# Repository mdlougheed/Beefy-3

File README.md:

# Meaty-3+
Meaty-3+ is a micro USB connected Basic Breakout for the FTDI FT231XS USB to serial IC. It's a "springboard" from the Sparkfun "Beefy-3" USB-Serial board with some additional capabilities.

Version 3 includes an improved micro-USB plug and updated documents.

Boards are available from OSH Park:<a href="https://oshpark.com/shared_projects/OyBMIKnf"></img></a>

The Meaty-3+ brings more power output, using a Torex Semiconductor 1 Amp XC6220B331MR-G linear 3.3V regulator. That's a whopping 66% power output increase (up to your USB power supply current limit - of course)! It also features on-board selectable CTS input or RTS output using a solder jumper.

This board will auto-reset any Arduino board that has the (DTR) reset pin brought out to a 6-pin connector (Arduino, Lilypad, etc) - AND can be configured for auto-resetting boards that use the RTS signal, as well as auto-reset/auto-program ESP-8266 & EPS-32 based boards that use the NodeMCU style DTR/RTS transistor crossover reset circuit (NodeMCU, ESP8266, ESP-01, Huzzah). In other words, you have flexibility!

This pluggable serial adapter, simplifies your application board when the power and cost expense of USB serial connectivity isn't always needed.

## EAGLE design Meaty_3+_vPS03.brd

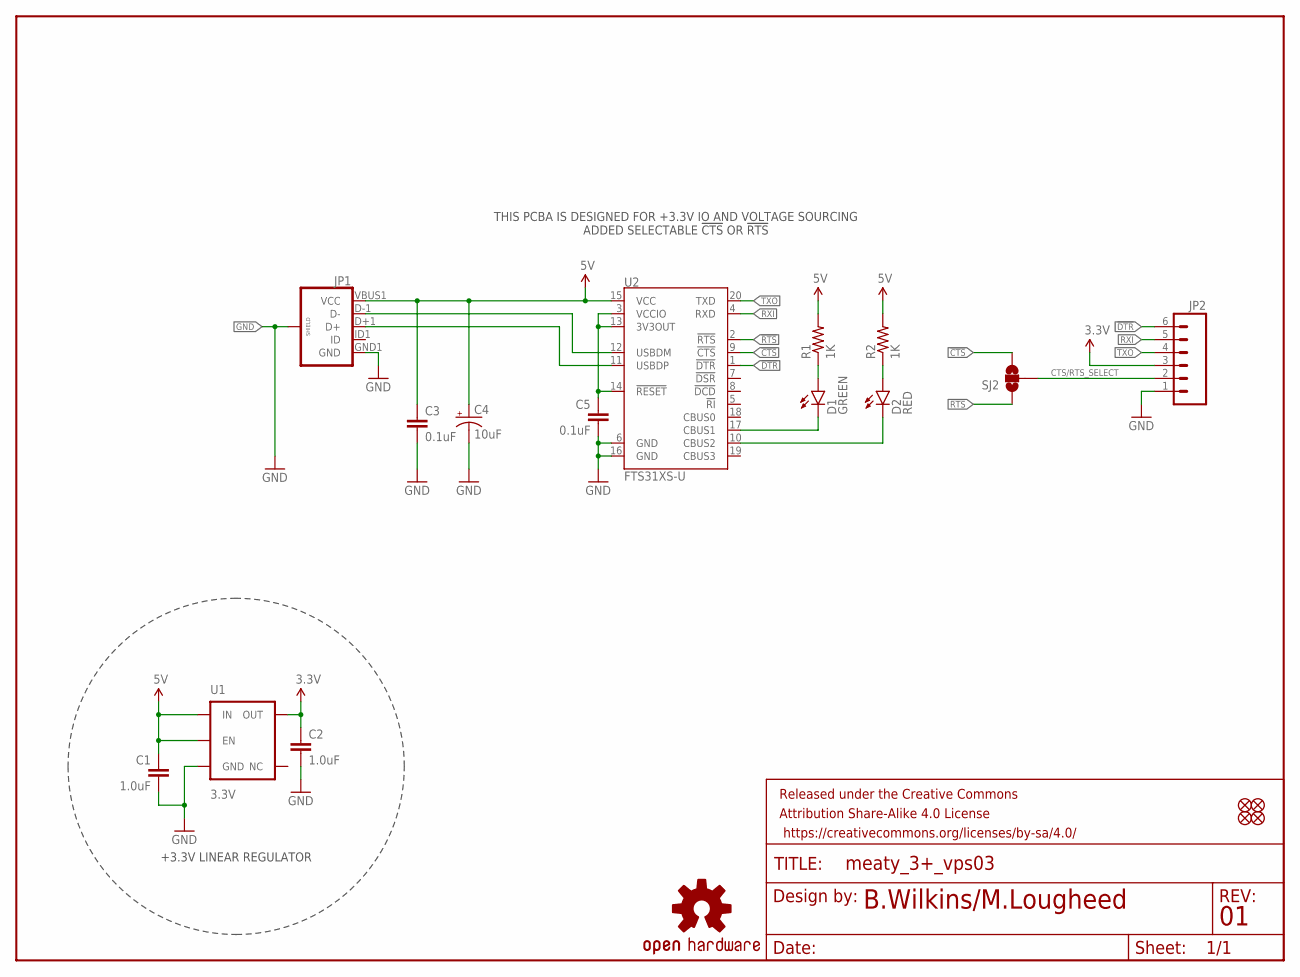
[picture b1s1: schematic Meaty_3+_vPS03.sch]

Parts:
C1, C2: 1.0uF; 0603-CAP
C3, C5: 0.1uF; 0603-CAP
C4: 10uF; EIA3216
D1: GREEN; LED-0603
D2: RED; LED-0603
FRAME1: FRAME-LETTER; CREATIVE_COMMONS
JP1: USB_MICROB_PLUGWE629105136821; MICRO-USB-2.0-B-SMT
JP2: M06SMD-FEMALE-V2; 1X06-SMD-FEMALE-V2
JP3, JP4, JP5, JP6: FIDUCIAL1X2; FIDUCIAL-1X2
LOGO1: OSHW-LOGOS; OSHW-LOGO-S
R1, R2: 1K; 0603-RES
SJ2: SOLDERJUMPER_2WAYS; SJ_3
U1: 3.3V; SOT23-5
U2: FTS31XS-U; SSOP20_L

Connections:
3V3: C2.1, JP2.3, U1.5 (OUT)
3V3LC: C5.1, U2.3 (VCCIO), U2.13 (3V3OUT), U2.14 (!RESET)
5V: C1.1, C3.1, C4.A (+), JP1.VBUS1 (VCC), R1.2, R2.2, U1.1 (IN), U1.3 (EN), U2.15 (VCC)
!CTS: SJ2.3, U2.9 (!CTS)
!DTR: JP2.6, U2.1 (!DTR)
!RTS: SJ2.1, U2.2 (!RTS)
CTS/RTS_SELECT: JP2.2, SJ2.2
GND: C1.2, C2.2, C3.2, C4.C (-), C5.2, JP1.GND1 (GND), JP1.SHIELD0 (SHIELD), JP1.SHIELD1 (SHIELD), JP1.SHIELD3 (SHIELD), JP2.1, U1.2 (GND), U2.6 (GND), U2.16 (GND)
unnamed: D2.A, R2.1
unnamed: D1.A, R1.1
RXI: JP2.5, U2.4 (RXD)
RXLED: D1.C, U2.17 (CBUS1)
TXLED: D2.C, U2.10 (CBUS2)
TXO: JP2.4, U2.20 (TXD)
USB_D+: JP1.D+1 (D+), U2.11 (USBDP)
USB_D-: JP1.D-1 (D-), U2.12 (USBDM)

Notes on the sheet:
+3.3V LINEAR REGULATOR
THIS PCBA IS DESIGNED FOR +3.3V IO AND VOLTAGE SOURCING ADDED SELECTABLE !CTS! OR !RTS!

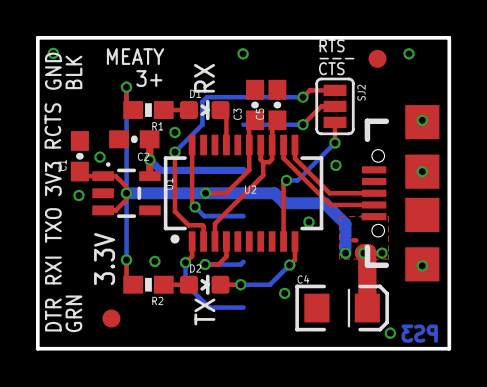
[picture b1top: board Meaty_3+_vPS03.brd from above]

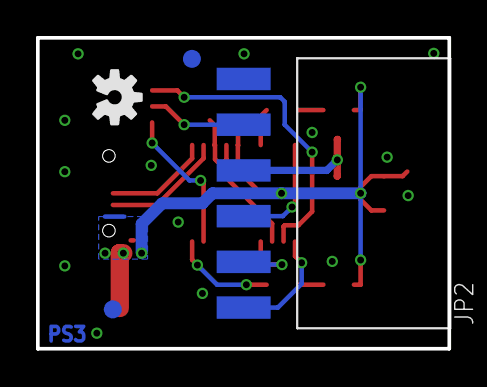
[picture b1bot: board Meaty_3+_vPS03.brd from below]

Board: 2 copper layers, 22.9 x 17.3 mm, 20 parts (4 on the bottom side), 16 nets.

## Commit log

2019-05-19 Initial Commit
    Eagle schematic and board files, plus BOM spreadsheet
2019-05-19 Update LICENSE

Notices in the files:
parts and their libraries:
SparkFun-Aesthetics: Licensing: CC v3.0 Share-Alike You are welcome to use this library for commercial purposes.
SparkFun-Aesthetics: Released under the Creative Commons Attribution Share-Alike 4.0 License
SparkFun-Aesthetics: https://creativecommons.org/licenses/by-sa/4.0
